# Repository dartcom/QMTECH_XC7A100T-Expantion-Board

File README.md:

# QMTECH_XC7A100T-Expantion-Board

Expantion board for the QMTECH_XC7A***T series for video processing learning.

This board contains 4 separate designs to save on cost. The boards can be ordered as a single board and then be scored with a fresh exacto knife along the dotted lines ( ! BEWARE to not breathe the FR4 dust as it is VERY harmful ! ).

The main board contains:
- 2 PMOD connectors.
- 2 24bit parallel video connectors. The left is meant to be an input and the right one an output.
- 1 micro sd card slot.
- 1 uart to usb converter.
- 1 usb PD 5v-2A input with overvoltage & overcurrent protection.
- 8 leds.

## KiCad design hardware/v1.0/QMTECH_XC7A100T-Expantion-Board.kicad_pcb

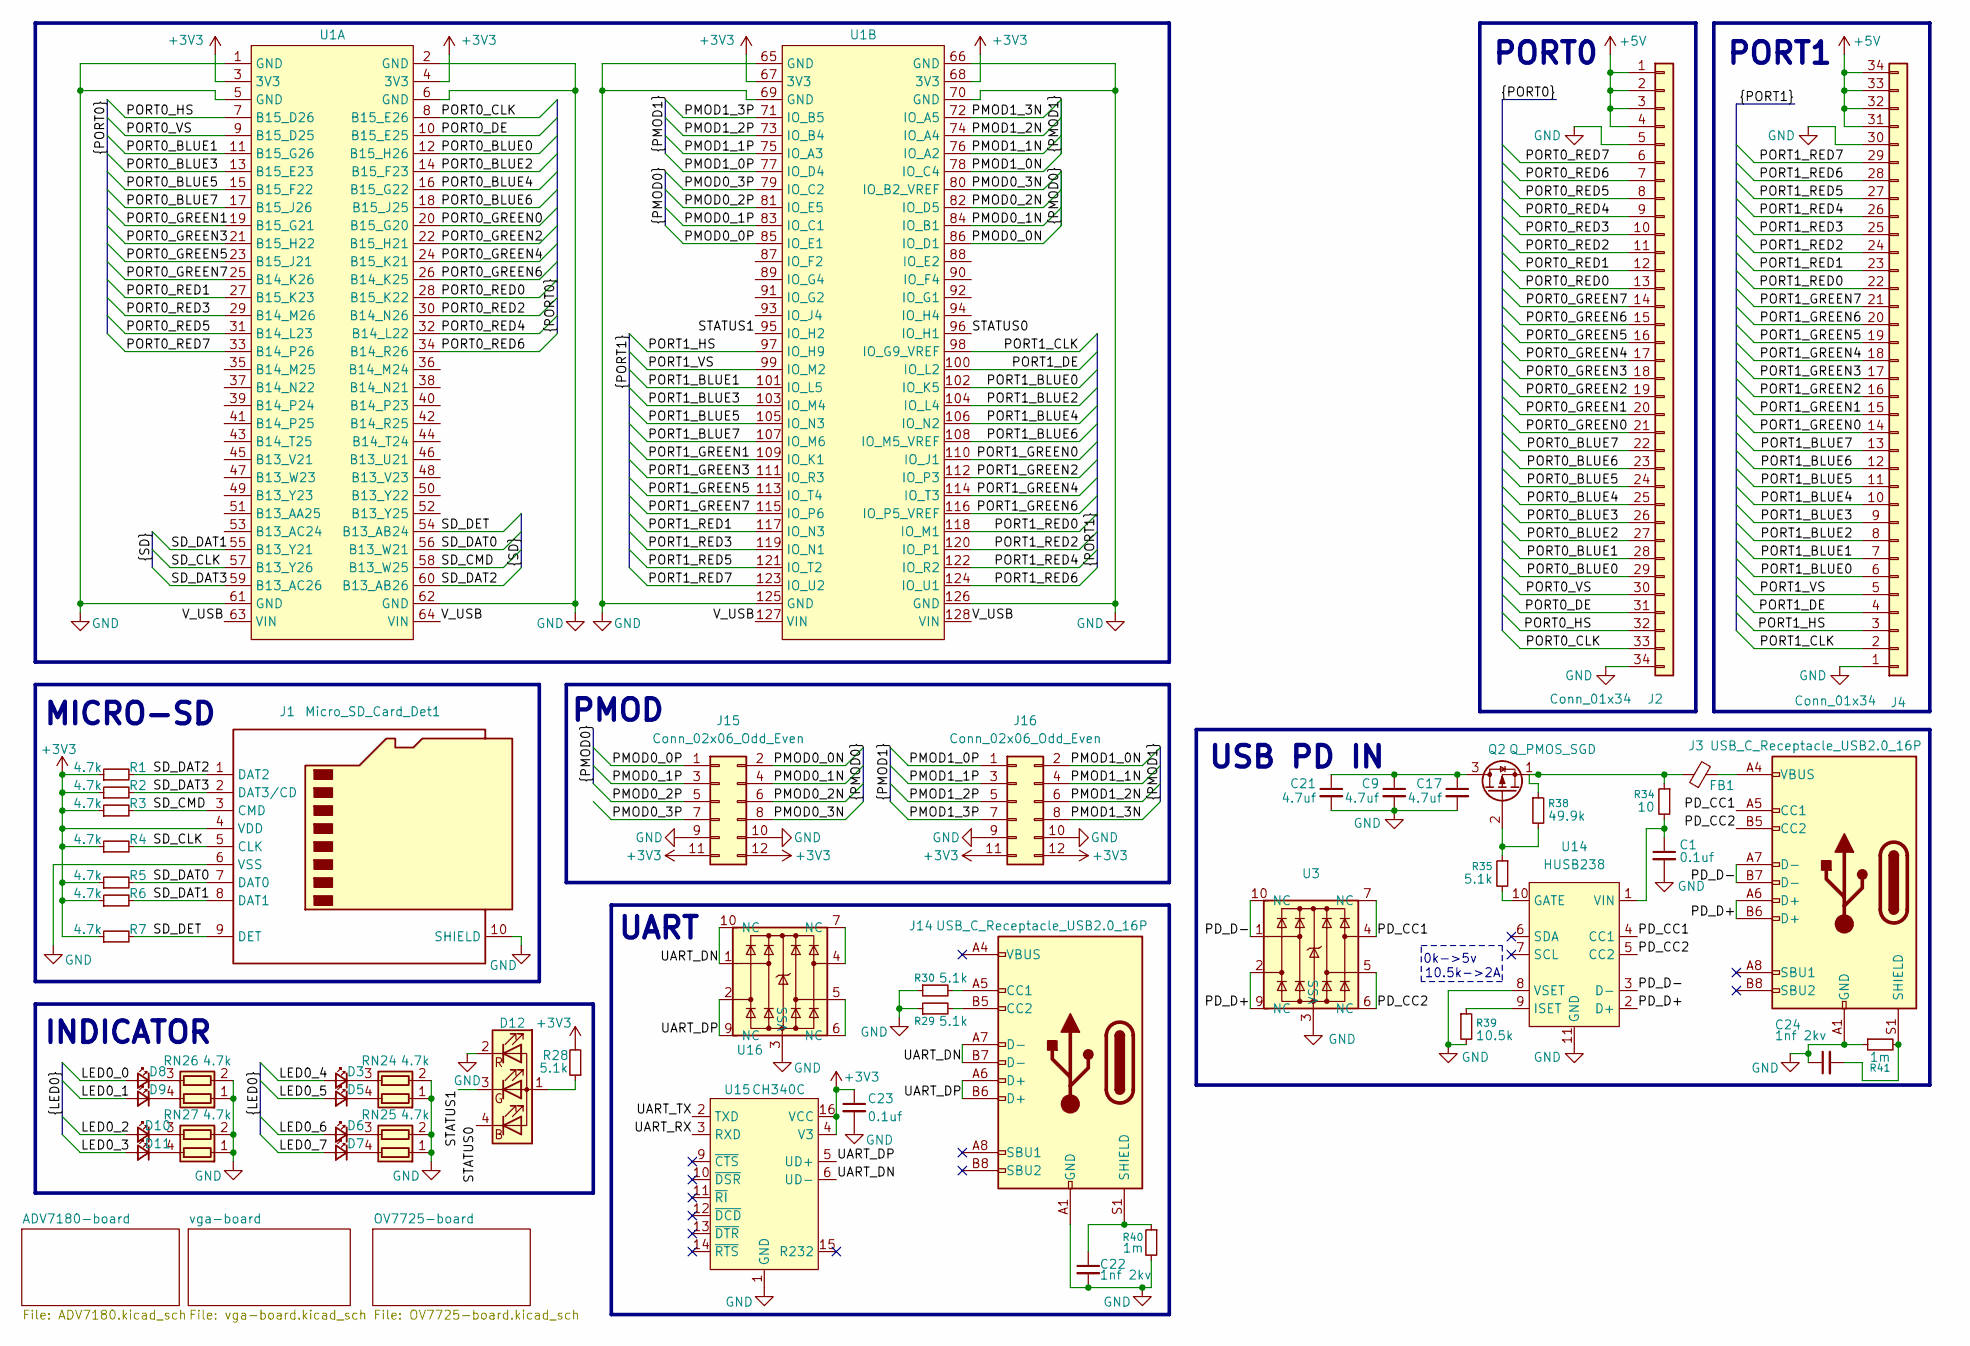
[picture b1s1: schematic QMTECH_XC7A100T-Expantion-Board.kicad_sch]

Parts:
C1, C23: 0.1uf
C9, C17, C21: 4.7uf
C22, C24: 1nf 2kv
D3, D5, D6, D7, D8, D9, D10, D11: LED_0805_2012Metric
D12: LED-SMD_4P-L1.6-W1.5-BR_TZ-P4-1615
FB1: (no value)
J1: Micro_SD_Card_Det1; TF-SMD_TF-PUSH
J2, J4: Conn_01x34; FPC-SMD_KH-FG0.5-H2.0-34PIN
J3, J14: USB_C_Receptacle_USB2.0_16P; USB_C_Receptacle_Palconn_UTC16-G
J15, J16: Conn_02x06_Odd_Even; PinSocket_2x06_P2.54mm_Horizontal
Q2: Q_PMOS_SGD; DFN-8-1EP_3x3mm_P0.5mm_EP1.7x2.4mm
R1, R2, R3, R4, R5, R6, R7: 4.7k; R_0603_1608Metric_Pad0.98x0.95mm_HandSolder
R28: 5.1k; R_0603_1608Metric_Pad0.98x0.95mm_HandSolder
R29, R30: 5.1k; R_0603_1608Metric
R34: 10
R35: 5.1k
R38: 49.9k
R39: 10.5k
R40, R41: 1m
RN24, RN25, RN26, RN27: 4.7k; R_Array_Convex_2x0603
U1: QMTECH_XC7A___T
U3, U16: Diodes_UDFN-10_1.0x2.5mm_P0.5mm
U14: HUSB238; DFN-10-1EP_3x3mm_P0.5mm_EP1.65x2.38mm_ThermalVias
U15: CH340C; SOIC-16_3.9x9.9mm_P1.27mm

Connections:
+3V3: C23.1, J1.4 (VDD), J15.11, J15.12, J16.11, J16.12, R1.1, R2.1, R3.1, R4.1, R5.1, R6.1, R7.1, R28.2, U1.3 (3V3), U1.4 (3V3), U1.67 (3V3), U1.68 (3V3), U15.4 (V3), U15.16 (VCC); also elsewhere on the board
+5V: J2.1, J2.2, J2.3, J2.4, J4.31, J4.32, J4.33, J4.34; also elsewhere on the board
/LED0_0: D8.2 (A)
/LED0_1: D9.2 (A)
/LED0_2: D10.2 (A)
/LED0_3: D11.2 (A)
/LED0_4: D3.2 (A)
/LED0_5: D5.2 (A)
/LED0_6: D6.2 (A)
/LED0_7: D7.2 (A)
/PD_CC1: J3.A5 (CC1), U3.4, U3.7 (NC), U14.4 (CC1)
/PD_CC2: J3.B5 (CC2), U3.5, U3.6 (NC), U14.5 (CC2)
/PD_D+: J3.A6 (D+), J3.B6 (D+), U3.2, U3.9 (NC), U14.2 (D+)
/PD_D-: J3.A7 (D-), J3.B7 (D-), U3.1, U3.10 (NC), U14.3 (D-)
/PMOD0_0N: J15.2, U1.86 (IO_D1)
/PMOD0_0P: J15.1, U1.85 (IO_E1)
/PMOD0_1N: J15.4, U1.84 (IO_B1)
/PMOD0_1P: J15.3, U1.83 (IO_C1)
/PMOD0_2N: J15.6, U1.82 (IO_D5)
/PMOD0_2P: J15.5, U1.81 (IO_E5)
/PMOD0_3N: J15.8, U1.80 (IO_B2_VREF)
/PMOD0_3P: J15.7, U1.79 (IO_C2)
/PMOD1_0N: J16.2, U1.78 (IO_C4)
/PMOD1_0P: J16.1, U1.77 (IO_D4)
/PMOD1_1N: J16.4, U1.76 (IO_A2)
/PMOD1_1P: J16.3, U1.75 (IO_A3)
/PMOD1_2N: J16.6, U1.74 (IO_A4)
/PMOD1_2P: J16.5, U1.73 (IO_B4)
/PMOD1_3N: J16.8, U1.72 (IO_A5)
/PMOD1_3P: J16.7, U1.71 (IO_B5)
/PORT0_BLUE0: J2.29, U1.12 (B15_H26)
/PORT0_BLUE1: J2.28, U1.11 (B15_G26)
/PORT0_BLUE2: J2.27, U1.14 (B15_F23)
/PORT0_BLUE3: J2.26, U1.13 (B15_E23)
/PORT0_BLUE4: J2.25, U1.16 (B15_G22)
/PORT0_BLUE5: J2.24, U1.15 (B15_F22)
/PORT0_BLUE6: J2.23, U1.18 (B15_J25)
/PORT0_BLUE7: J2.22, U1.17 (B15_J26)
/PORT0_CLK: J2.33, U1.8 (B15_E26)
/PORT0_DE: J2.31, U1.10 (B15_E25)
/PORT0_GREEN0: J2.21, U1.20 (B15_G20)
/PORT0_GREEN1: J2.20, U1.19 (B15_G21)
/PORT0_GREEN2: J2.19, U1.22 (B15_H21)
/PORT0_GREEN3: J2.18, U1.21 (B15_H22)
/PORT0_GREEN4: J2.17, U1.24 (B15_K21)
/PORT0_GREEN5: J2.16, U1.23 (B15_J21)
/PORT0_GREEN6: J2.15, U1.26 (B14_K25)
/PORT0_GREEN7: J2.14, U1.25 (B14_K26)
/PORT0_HS: J2.32, U1.7 (B15_D26)
/PORT0_RED0: J2.13, U1.28 (B15_K22)
/PORT0_RED1: J2.12, U1.27 (B15_K23)
/PORT0_RED2: J2.11, U1.30 (B14_N26)
/PORT0_RED3: J2.10, U1.29 (B14_M26)
/PORT0_RED4: J2.9, U1.32 (B14_L22)
/PORT0_RED5: J2.8, U1.31 (B14_L23)
/PORT0_RED6: J2.7, U1.34 (B14_R26)
/PORT0_RED7: J2.6, U1.33 (B14_P26)
/PORT0_VS: J2.30, U1.9 (B15_D25)
/PORT1_BLUE0: J4.6, U1.102 (IO_K5)
/PORT1_BLUE1: J4.7, U1.101 (IO_L5)
/PORT1_BLUE2: J4.8, U1.104 (IO_L4)
/PORT1_BLUE3: J4.9, U1.103 (IO_M4)
/PORT1_BLUE4: J4.10, U1.106 (IO_N2)
/PORT1_BLUE5: J4.11, U1.105 (IO_N3)
/PORT1_BLUE6: J4.12, U1.108 (IO_M5_VREF)
/PORT1_BLUE7: J4.13, U1.107 (IO_M6)
/PORT1_CLK: J4.2, U1.98 (IO_G9_VREF)
/PORT1_DE: J4.4, U1.100 (IO_L2)
/PORT1_GREEN0: J4.14, U1.110 (IO_J1)
/PORT1_GREEN1: J4.15, U1.109 (IO_K1)
/PORT1_GREEN2: J4.16, U1.112 (IO_P3)
/PORT1_GREEN3: J4.17, U1.111 (IO_R3)
/PORT1_GREEN4: J4.18, U1.114 (IO_T3)
/PORT1_GREEN5: J4.19, U1.113 (IO_T4)
/PORT1_GREEN6: J4.20, U1.116 (IO_P5_VREF)
/PORT1_GREEN7: J4.21, U1.115 (IO_P6)
/PORT1_HS: J4.3, U1.97 (IO_H9)
/PORT1_RED0: J4.22, U1.118 (IO_M1)
/PORT1_RED1: J4.23, U1.117 (IO_N3)
/PORT1_RED2: J4.24, U1.120 (IO_P1)
/PORT1_RED3: J4.25, U1.119 (IO_N1)
/PORT1_RED4: J4.26, U1.122 (IO_R2)
/PORT1_RED5: J4.27, U1.121 (IO_T2)
/PORT1_RED6: J4.28, U1.124 (IO_U1)
/PORT1_RED7: J4.29, U1.123 (IO_U2)
/PORT1_VS: J4.5, U1.99 (IO_M2)
/SD_CLK: J1.5 (CLK), R4.2, U1.57 (B13_Y26)
/SD_CMD: J1.3 (CMD), R3.2, U1.58 (B13_W25)
/SD_DAT0: J1.7 (DAT0), R5.2, U1.56 (B13_W21)
/SD_DAT1: J1.8 (DAT1), R6.2, U1.55 (B13_Y21)
/SD_DAT2: J1.1 (DAT2), R1.2, U1.60 (B13_AB26)
/SD_DAT3: J1.2 (DAT3/CD), R2.2, U1.59 (B13_AC26)
/SD_DET: J1.9 (DET), R7.2, U1.54 (B13_AB24)
/STATUS0: D12.4 (BK), U1.96 (IO_H1)
/STATUS1: D12.3 (GK), U1.95 (IO_H2)
/UART_DN: J14.A7 (D-), J14.B7 (D-), U15.6 (UD-), U16.1, U16.10 (NC)
/UART_DP: J14.A6 (D+), J14.B6 (D+), U15.5 (UD+), U16.2, U16.9 (NC)
/UART_RX: U15.3 (RXD)
/UART_TX: U15.2 (TXD)
/V_USB: U1.63 (VIN), U1.64 (VIN), U1.127 (VIN), U1.128 (VIN)
GND: C1.2, C9.2, C17.2, C21.2, C22.2, C23.2, C24.1, D12.2 (RK), J1.6 (VSS), J1.10 (SHIELD), J2.5, J2.34, J3.A1 (GND), J3.A12 (GND), J3.B1 (GND), J3.B12 (GND), J4.1, J4.30, J14.A1 (GND), J14.A12 (GND), J14.B1 (GND), J14.B12 (GND), J15.9, J15.10, J16.9, J16.10, R29.1, R30.1, R39.2, R40.2, R41.1, RN24.1 (R1.1), RN24.2 (R2.1), RN25.1 (R1.1), RN25.2 (R2.1), RN26.1 (R1.1), RN26.2 (R2.1), RN27.1 (R1.1), RN27.2 (R2.1), U1.1 (GND), U1.2 (GND), U1.5 (GND), U1.6 (GND), U1.61 (GND), U1.62 (GND), U1.65 (GND), U1.66 (GND), U1.69 (GND), U1.70 (GND), U1.125 (GND), U1.126 (GND), U3.3 (VSS), U3.8 (VSS), U14.8 (VSET), U14.11 (GND), U15.1 (GND), U16.3 (VSS), U16.8 (VSS); also elsewhere on the board
unnamed: D3.1 (K), RN24.3 (R2.2)
unnamed: D5.1 (K), RN24.4 (R1.2)
unnamed: D6.1 (K), RN25.3 (R2.2)
unnamed: D7.1 (K), RN25.4 (R1.2)
unnamed: D8.1 (K), RN26.3 (R2.2)
unnamed: D9.1 (K), RN26.4 (R1.2)
unnamed: D10.1 (K), RN27.3 (R2.2)
unnamed: D11.1 (K), RN27.4 (R1.2)
unnamed: D12.1 (A), R28.1
unnamed: FB1.2, J3.A4 (VBUS), J3.A9 (VBUS), J3.B4 (VBUS), J3.B9 (VBUS)
unnamed: C24.2, J3.S1 (SHIELD), R41.2
unnamed: J14.A5 (CC1), R30.2
unnamed: J14.B5 (CC2), R29.2
unnamed: C22.1, J14.S1 (SHIELD), R40.1
unnamed: C9.1, C17.1, C21.1, Q2.3 (D)
unnamed: Q2.2 (G), R35.1, R38.2
unnamed: FB1.1, Q2.1 (S), R34.1, R38.1
unnamed: R35.2, U14.10 (GATE)
unnamed: R39.1, U14.9 (ISET)
unnamed: C1.1, R34.2, U14.1 (VIN)
unnamed: U16.5, U16.6 (NC)
unnamed: U16.4, U16.7 (NC)

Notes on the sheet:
PORT0
PORT1
PMOD
MICRO-SD
10.5k->2A
UART
USB PD IN
0k->5v
INDICATOR

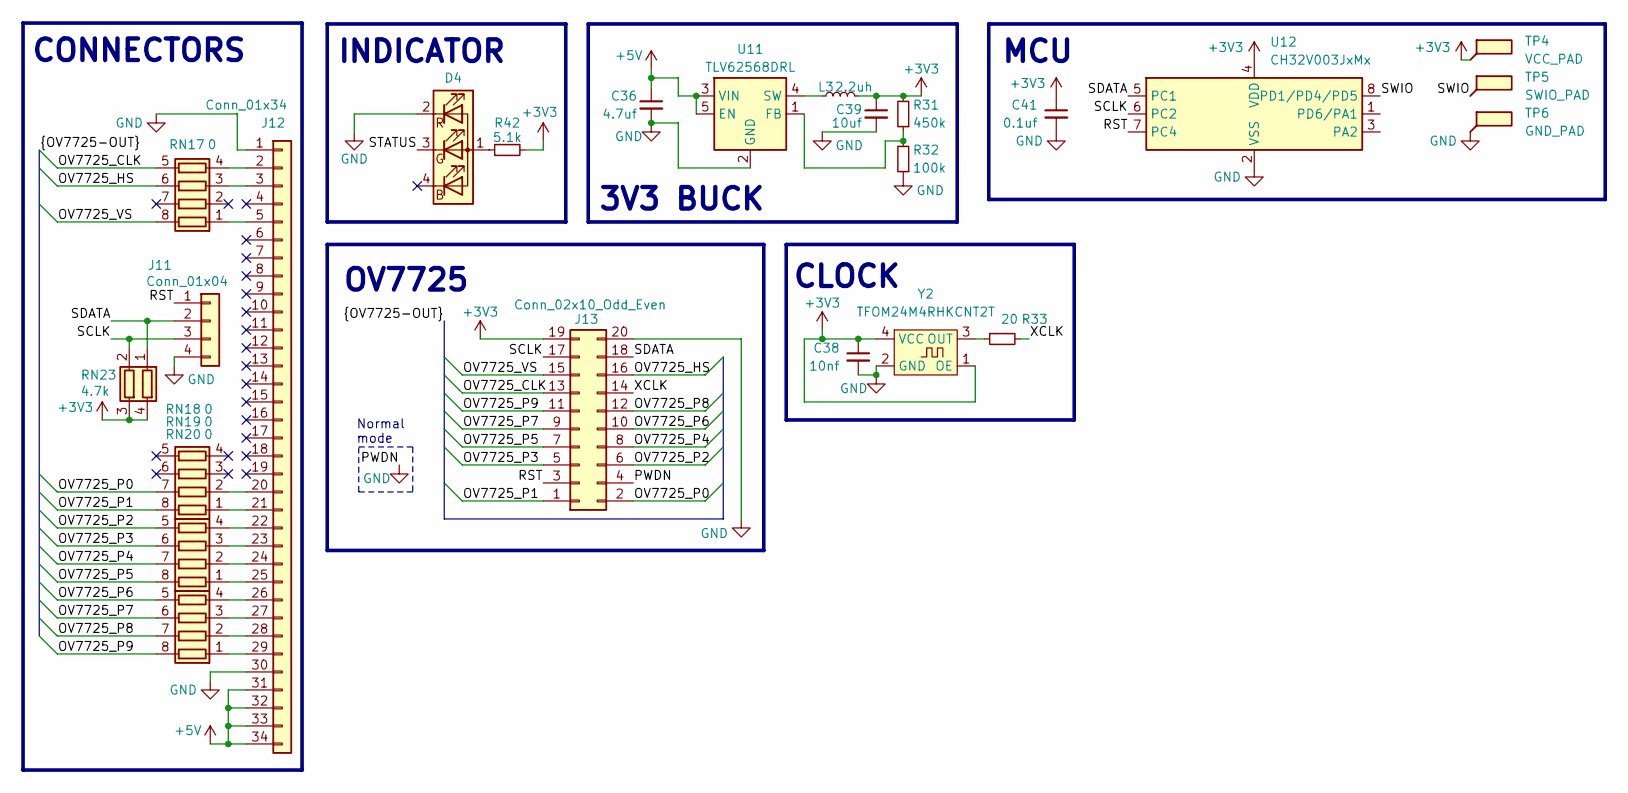
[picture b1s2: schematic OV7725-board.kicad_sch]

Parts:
C36: 4.7uf; C_0603_1608Metric
C38: 10nf; C_0603_1608Metric
C39: 10uf; C_0603_1608Metric
C41: 0.1uf; C_0603_1608Metric
D4: LED-SMD_4P-L1.6-W1.5-BR_TZ-P4-1615
J11: Conn_01x04; PinHeader_1x04_P2.54mm_Vertical
J12: Conn_01x34; FPC-SMD_KH-FG0.5-H2.0-34PIN
J13: Conn_02x10_Odd_Even; PinSocket_2x10_P2.54mm_Vertical
L3: 2.2uh; L_0603_1608Metric
R31: 450k; R_0603_1608Metric
R32: 100k; R_0603_1608Metric
R33: 20; R_0603_1608Metric
R42: 5.1k; R_0603_1608Metric
RN17, RN18, RN19, RN20: 0; R_Array_Convex_4x0603
RN23: 4.7k; R_Array_Convex_2x0603
TP4: VCC_PAD; TestPoint_Pad_D1.5mm
TP5: SWIO_PAD; TestPoint_Pad_D1.5mm
TP6: GND_PAD; TestPoint_Pad_D1.5mm
U11: TLV62568DRL; SOT-563
U12: CH32V003JxMx; SOP-8_3.9x4.9mm_P1.27mm
Y2: TFOM24M4RHKCNT2T

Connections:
+3V3: C38.1, C39.1, C41.1, J13.19, L3.2, R31.2, R42.2, RN23.3 (R2.2), RN23.4 (R1.2), TP4.1, U12.4 (VDD), Y2.1 (OE), Y2.4 (VCC); also elsewhere on the board
+5V: C36.1, J12.31, J12.32, J12.33, J12.34, U11.3 (VIN), U11.5 (EN); also elsewhere on the board
/OV7725-board/OV7725_CLK: J13.13, RN17.5 (R4.2)
/OV7725-board/OV7725_HS: J13.16, RN17.6 (R3.2)
/OV7725-board/OV7725_P0: J13.2, RN18.7 (R2.2)
/OV7725-board/OV7725_P1: J13.1, RN18.8 (R1.2)
/OV7725-board/OV7725_P2: J13.6, RN19.5 (R4.2)
/OV7725-board/OV7725_P3: J13.5, RN19.6 (R3.2)
/OV7725-board/OV7725_P4: J13.8, RN19.7 (R2.2)
/OV7725-board/OV7725_P5: J13.7, RN19.8 (R1.2)
/OV7725-board/OV7725_P6: J13.10, RN20.5 (R4.2)
/OV7725-board/OV7725_P7: J13.9, RN20.6 (R3.2)
/OV7725-board/OV7725_P8: J13.12, RN20.7 (R2.2)
/OV7725-board/OV7725_P9: J13.11, RN20.8 (R1.2)
/OV7725-board/OV7725_VS: J13.15, RN17.8 (R1.2)
/OV7725-board/RST: J11.1, J13.3, U12.7 (PC4)
/OV7725-board/SCLK: J11.3, J13.17, RN23.2 (R2.1), U12.6 (PC2)
/OV7725-board/SDATA: J11.2, J13.18, RN23.1 (R1.1), U12.5 (PC1)
/OV7725-board/STATUS: D4.3 (GK)
/OV7725-board/SWIO: TP5.1, U12.8 (PD1/PD4/PD5)
/OV7725-board/XCLK: J13.14, R33.2
GND: C36.2, C38.2, C39.2, C41.2, D4.2 (RK), J11.4, J12.1, J12.30, J13.4, J13.20, R32.1, TP6.1, U11.2 (GND), U12.2 (VSS), Y2.2 (GND); also elsewhere on the board
unnamed: D4.1 (A), R42.1
unnamed: J12.2, RN17.4 (R4.1)
unnamed: J12.3, RN17.3 (R3.1)
unnamed: J12.5, RN17.1 (R1.1)
unnamed: J12.20, RN18.2 (R2.1)
unnamed: J12.21, RN18.1 (R1.1)
unnamed: J12.22, RN19.4 (R4.1)
unnamed: J12.23, RN19.3 (R3.1)
unnamed: J12.24, RN19.2 (R2.1)
unnamed: J12.25, RN19.1 (R1.1)
unnamed: J12.26, RN20.4 (R4.1)
unnamed: J12.27, RN20.3 (R3.1)
unnamed: J12.28, RN20.2 (R2.1)
unnamed: J12.29, RN20.1 (R1.1)
unnamed: R31.1, R32.2, U11.1 (FB)
unnamed: L3.1, U11.4 (SW)
unnamed: R33.1, Y2.3 (OUT)

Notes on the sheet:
CLOCK
MCU
OV7725
INDICATOR
Normal mode
CONNECTORS
3V3 BUCK

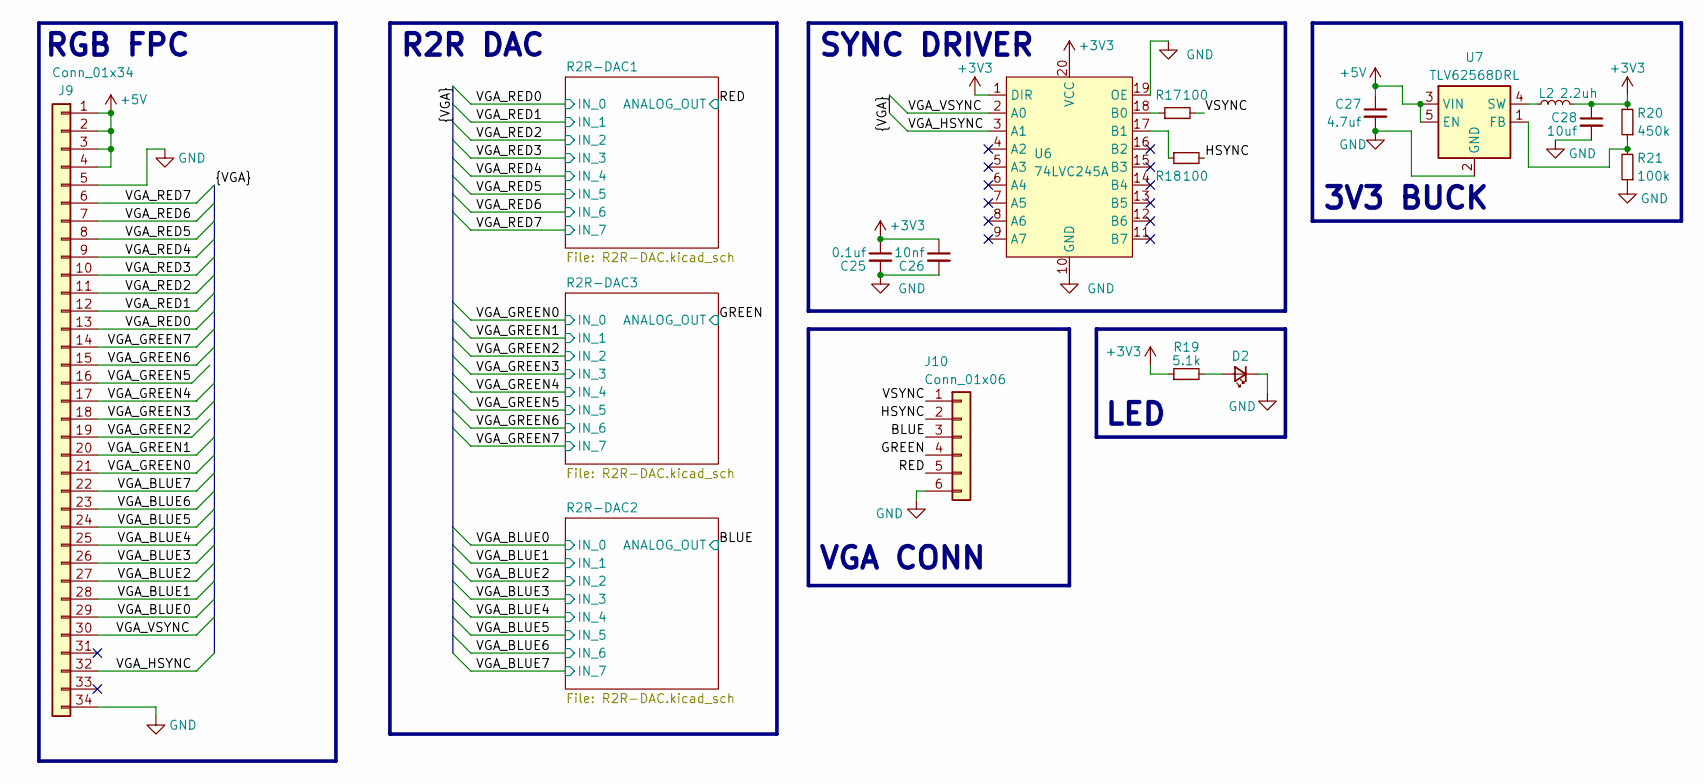
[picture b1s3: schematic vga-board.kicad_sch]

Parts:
C25: 0.1uf; C_0603_1608Metric
C26: 10nf; C_0603_1608Metric
C27: 4.7uf; C_0603_1608Metric
C28: 10uf; C_0603_1608Metric
D2: LED_0402_1005Metric_Pad0.77x0.64mm_HandSolder
J9: Conn_01x34; FPC-SMD_KH-FG0.5-H2.0-34PIN
J10: Conn_01x06; PinHeader_1x06_P2.54mm_Vertical
L2: 2.2uh; L_0603_1608Metric
R17, R18: 100; R_0603_1608Metric
R19: 5.1k; R_0603_1608Metric
R20: 450k; R_0603_1608Metric
R21: 100k; R_0603_1608Metric
U6: 74LVC245A; TSSOP-20_4.4x6.5mm_P0.65mm
U7: TLV62568DRL; SOT-563

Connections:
+3V3: C25.1, C26.1, C28.1, L2.2, R19.1, R20.2, U6.1 (DIR), U6.20 (VCC); also elsewhere on the board
+5V: C27.1, J9.1, J9.2, J9.3, J9.4, U7.3 (VIN), U7.5 (EN); also elsewhere on the board
/vga-board/BLUE: J10.3; also elsewhere on the board
/vga-board/GREEN: J10.4; also elsewhere on the board
/vga-board/HSYNC: J10.2, R18.2
/vga-board/RED: J10.5; also elsewhere on the board
/vga-board/VGA_BLUE0: J9.29; also elsewhere on the board
/vga-board/VGA_BLUE1: J9.28; also elsewhere on the board
/vga-board/VGA_BLUE2: J9.27; also elsewhere on the board
/vga-board/VGA_BLUE3: J9.26; also elsewhere on the board
/vga-board/VGA_BLUE4: J9.25; also elsewhere on the board
/vga-board/VGA_BLUE5: J9.24; also elsewhere on the board
/vga-board/VGA_BLUE6: J9.23; also elsewhere on the board
/vga-board/VGA_BLUE7: J9.22; also elsewhere on the board
/vga-board/VGA_GREEN0: J9.21; also elsewhere on the board
/vga-board/VGA_GREEN1: J9.20; also elsewhere on the board
/vga-board/VGA_GREEN2: J9.19; also elsewhere on the board
/vga-board/VGA_GREEN3: J9.18; also elsewhere on the board
/vga-board/VGA_GREEN4: J9.17; also elsewhere on the board
/vga-board/VGA_GREEN5: J9.16; also elsewhere on the board
/vga-board/VGA_GREEN6: J9.15; also elsewhere on the board
/vga-board/VGA_GREEN7: J9.14; also elsewhere on the board
/vga-board/VGA_HSYNC: J9.32, U6.3 (A1)
/vga-board/VGA_RED0: J9.13; also elsewhere on the board
/vga-board/VGA_RED1: J9.12; also elsewhere on the board
/vga-board/VGA_RED2: J9.11; also elsewhere on the board
/vga-board/VGA_RED3: J9.10; also elsewhere on the board
/vga-board/VGA_RED4: J9.9; also elsewhere on the board
/vga-board/VGA_RED5: J9.8; also elsewhere on the board
/vga-board/VGA_RED6: J9.7; also elsewhere on the board
/vga-board/VGA_RED7: J9.6; also elsewhere on the board
/vga-board/VGA_VSYNC: J9.30, U6.2 (A0)
/vga-board/VSYNC: J10.1, R17.2
GND: C25.2, C26.2, C27.2, C28.2, D2.1 (K), J9.5, J9.34, J10.6, R21.1, U6.10 (GND), U6.19 (OE), U7.2 (GND); also elsewhere on the board
unnamed: D2.2 (A), R19.2
unnamed: R17.1, U6.18 (B0)
unnamed: R18.1, U6.17 (B1)
unnamed: R20.1, R21.2, U7.1 (FB)
unnamed: L2.1, U7.4 (SW)

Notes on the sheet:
R2R DAC
LED
3V3 BUCK
RGB FPC
SYNC DRIVER
VGA CONN

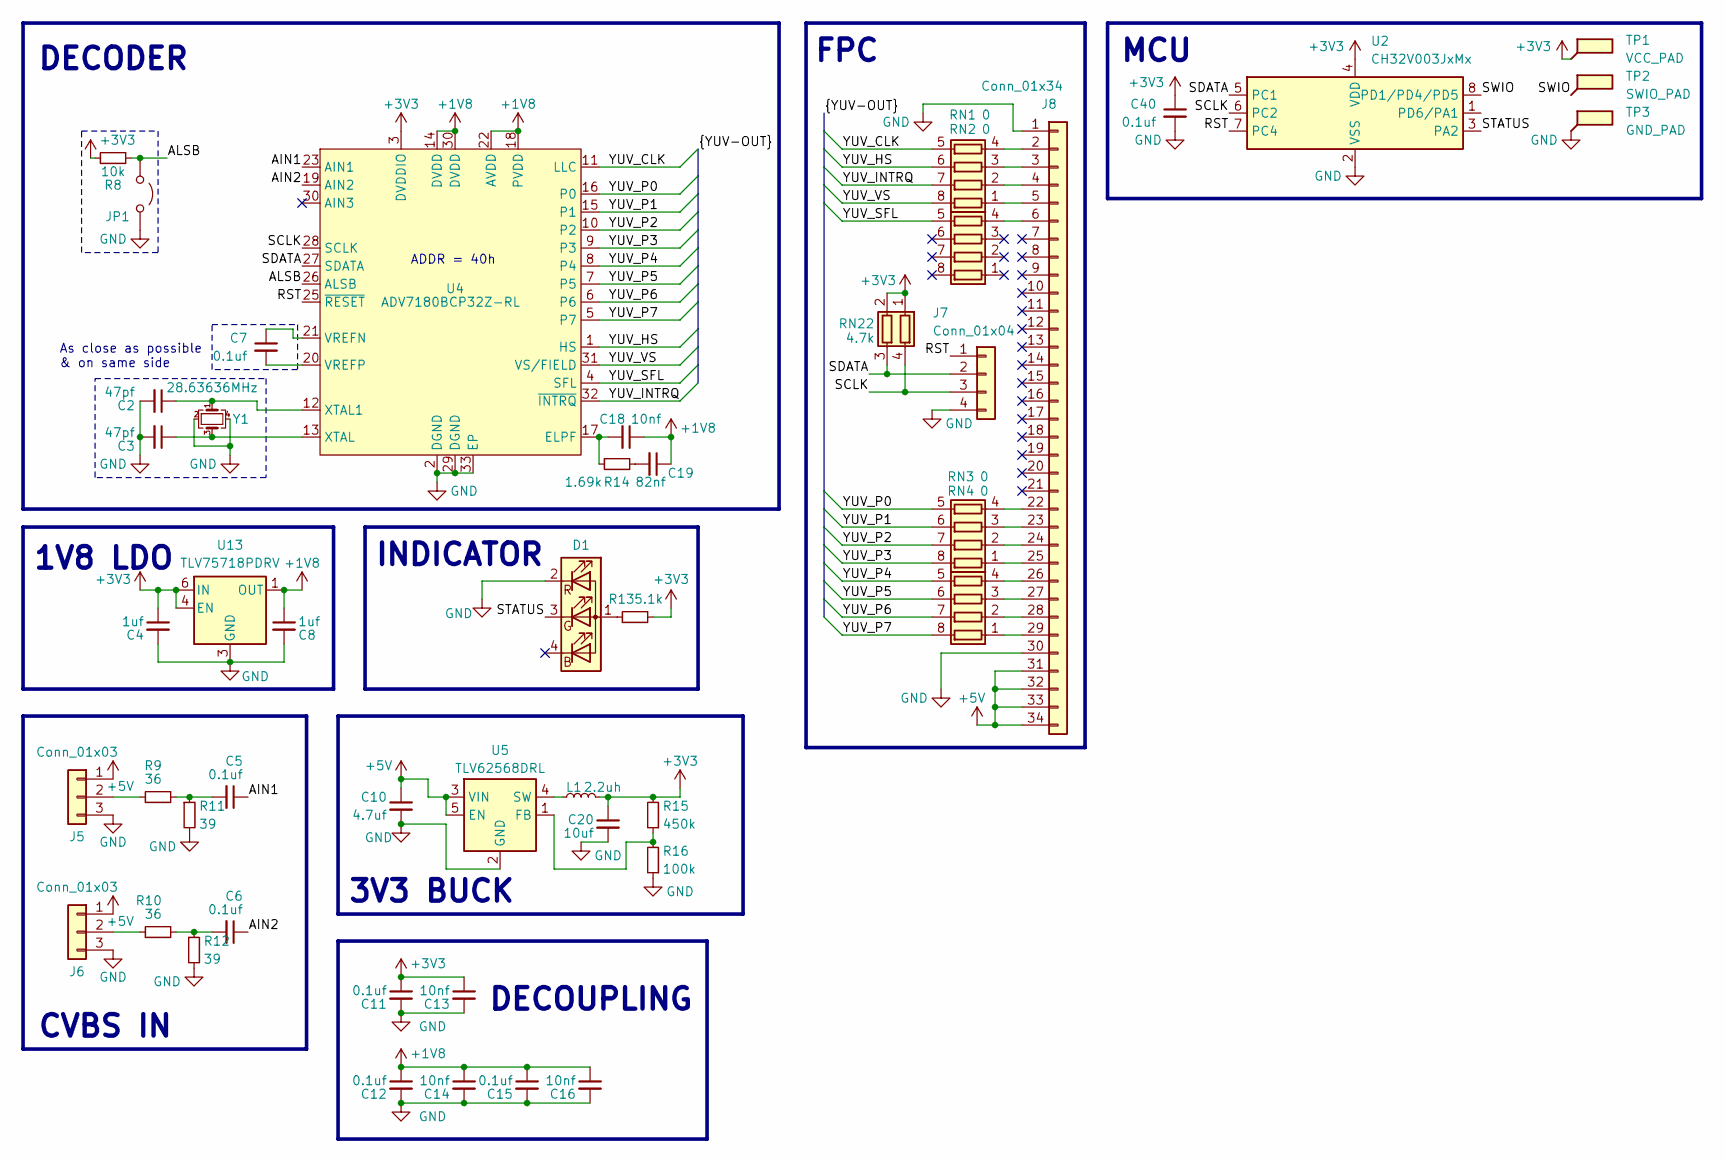
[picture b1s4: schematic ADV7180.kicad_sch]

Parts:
C2, C3: 47pf; C_0603_1608Metric
C4, C8: 1uf; C_0603_1608Metric
C5, C6, C7, C11, C12, C15, C40: 0.1uf; C_0603_1608Metric
C10: 4.7uf; C_0603_1608Metric
C13, C14, C16, C18: 10nf; C_0603_1608Metric
C19: 82nf; C_0603_1608Metric
C20: 10uf; C_0603_1608Metric
D1: LED-SMD_4P-L1.6-W1.5-BR_TZ-P4-1615
J5, J6: Conn_01x03; PinHeader_1x03_P2.54mm_Vertical
J7: Conn_01x04; PinHeader_1x04_P2.54mm_Vertical
J8: Conn_01x34; FPC-SMD_KH-FG0.5-H2.0-34PIN
JP1: SolderJumper-2_P1.3mm_Open_RoundedPad1.0x1.5mm
L1: 2.2uh; L_0603_1608Metric
R8: 10k; R_0603_1608Metric
R9, R10: 36; R_0603_1608Metric
R11, R12: 39; R_0603_1608Metric
R13: 5.1k; R_0603_1608Metric
R14: 1.69k; R_0603_1608Metric
R15: 450k; R_0603_1608Metric
R16: 100k; R_0603_1608Metric
RN1, RN2, RN3, RN4: 0; R_Array_Convex_4x0603
RN22: 4.7k; R_Array_Convex_2x0603
TP1: VCC_PAD; TestPoint_Pad_D1.5mm
TP2: SWIO_PAD; TestPoint_Pad_D1.5mm
TP3: GND_PAD; TestPoint_Pad_D1.5mm
U2: CH32V003JxMx; SOP-8_3.9x4.9mm_P1.27mm
U4: ADV7180BCP32Z-RL; LFCSP-32-1EP_5x5mm_P0.5mm_EP3.6x3.6mm; LCSC Part C459884
U5: TLV62568DRL; SOT-563
U13: TLV75718PDRV; WSON-6-1EP_2x2mm_P0.65mm_EP1x1.6mm
Y1: 28.63636MHz; Crystal_SMD_Abracon_ABM8AIG-4Pin_3.2x2.5mm

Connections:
+1V8: C8.1, C12.1, C14.1, C15.1, C16.1, C18.1, C19.1, U4.14 (DVDD), U4.18 (PVDD), U4.22 (AVDD), U4.30 (DVDD), U13.1 (OUT)
+3V3: C4.1, C11.1, C13.1, C20.1, C40.1, L1.2, R8.2, R13.2, R15.2, RN22.1 (R1.1), RN22.2 (R2.1), TP1.1, U2.4 (VDD), U4.3 (DVDDIO), U13.4 (EN), U13.6 (IN); also elsewhere on the board
+5V: C10.1, J5.1, J6.1, J8.31, J8.32, J8.33, J8.34, U5.3 (VIN), U5.5 (EN); also elsewhere on the board
/ADV7180-board/AIN1: C5.1, U4.23 (AIN1)
/ADV7180-board/AIN2: C6.1, U4.19 (AIN2)
/ADV7180-board/ALSB: JP1.2 (B), R8.1, U4.26 (ALSB)
/ADV7180-board/RST: J7.1, U2.7 (PC4), U4.25 (~RESET)
/ADV7180-board/SCLK: J7.3, RN22.4 (R1.2), U2.6 (PC2), U4.28 (SCLK)
/ADV7180-board/SDATA: J7.2, RN22.3 (R2.2), U2.5 (PC1), U4.27 (SDATA)
/ADV7180-board/STATUS: D1.3 (GK), U2.3 (PA2)
/ADV7180-board/SWIO: TP2.1, U2.8 (PD1/PD4/PD5)
/ADV7180-board/YUV_CLK: RN1.5 (R4.2), U4.11 (LLC)
/ADV7180-board/YUV_HS: RN1.6 (R3.2), U4.1 (HS)
/ADV7180-board/YUV_INTRQ: RN1.7 (R2.2), U4.32 (~INTRQ)
/ADV7180-board/YUV_P0: RN3.5 (R4.2), U4.16 (P0)
/ADV7180-board/YUV_P1: RN3.6 (R3.2), U4.15 (P1)
/ADV7180-board/YUV_P2: RN3.7 (R2.2), U4.10 (P2)
/ADV7180-board/YUV_P3: RN3.8 (R1.2), U4.9 (P3)
/ADV7180-board/YUV_P4: RN4.5 (R4.2), U4.8 (P4)
/ADV7180-board/YUV_P5: RN4.6 (R3.2), U4.7 (P5)
/ADV7180-board/YUV_P6: RN4.7 (R2.2), U4.6
/ADV7180-board/YUV_P7: RN4.8 (R1.2), U4.5 (P7)
/ADV7180-board/YUV_SFL: RN2.5 (R4.2), U4.4 (SFL)
/ADV7180-board/YUV_VS: RN1.8 (R1.2), U4.31 (VS/FIELD)
GND: C2.2, C3.2, C4.2, C8.2, C10.2, C11.2, C12.2, C13.2, C14.2, C15.2, C16.2, C20.2, C40.2, D1.2 (RK), J5.3, J6.3, J7.4, J8.1, J8.30, JP1.1 (A), R11.2, R12.2, R16.1, TP3.1, U2.2 (VSS), U4.2 (DGND), U4.29 (DGND), U4.33 (EP), U5.2 (GND), U13.3 (GND), U13.7 (GND), Y1.2, Y1.4; also elsewhere on the board
unnamed: C5.2, R9.2, R11.1
unnamed: C6.2, R10.2, R12.1
unnamed: C19.2, R14.2
unnamed: D1.1 (A), R13.1
unnamed: J5.2, R9.1
unnamed: J6.2, R10.1
unnamed: J8.2, RN1.4 (R4.1)
unnamed: J8.3, RN1.3 (R3.1)
unnamed: J8.4, RN1.2 (R2.1)
unnamed: J8.5, RN1.1 (R1.1)
unnamed: J8.6, RN2.4 (R4.1)
unnamed: J8.22, RN3.4 (R4.1)
unnamed: J8.23, RN3.3 (R3.1)
unnamed: J8.24, RN3.2 (R2.1)
unnamed: J8.25, RN3.1 (R1.1)
unnamed: J8.26, RN4.4 (R4.1)
unnamed: J8.27, RN4.3 (R3.1)
unnamed: J8.28, RN4.2 (R2.1)
unnamed: J8.29, RN4.1 (R1.1)
unnamed: C18.2, R14.1, U4.17 (ELPF)
unnamed: C7.1, U4.21 (VREFN)
unnamed: C7.2, U4.20 (VREFP)
unnamed: C2.1, U4.12 (XTAL1), Y1.1
unnamed: C3.1, U4.13 (XTAL), Y1.3
unnamed: R15.1, R16.2, U5.1 (FB)
unnamed: L1.1, U5.4 (SW)

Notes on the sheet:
3V3 BUCK
As close as possible & on same side
1V8 LDO
FPC
MCU
ADDR = 40h
DECOUPLING
INDICATOR
DECODER
CVBS IN

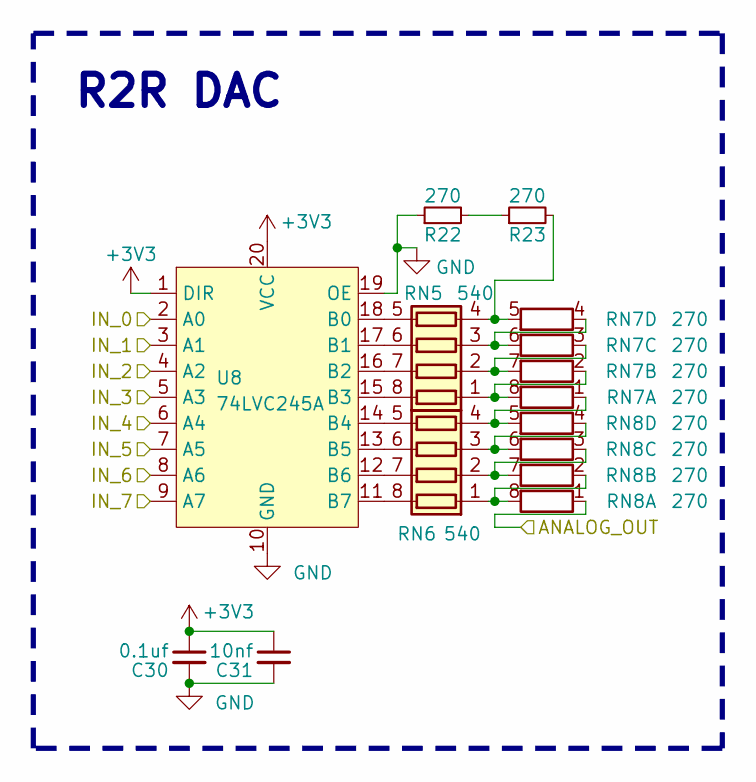
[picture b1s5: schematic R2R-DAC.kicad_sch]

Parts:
C30: 0.1uf; C_0603_1608Metric
C31: 10nf; C_0603_1608Metric
R22, R23: 270; R_0603_1608Metric
RN5, RN6: 540; R_Array_Convex_4x0603
RN7, RN8: 270; R_Array_Convex_4x0603
U8: 74LVC245A; TSSOP-20_4.4x6.5mm_P0.65mm

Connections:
+3V3: C30.1, C31.1, U8.1 (DIR), U8.20 (VCC); also elsewhere on the board
/vga-board/RED: RN8.1 (R1.1); also elsewhere on the board
/vga-board/VGA_RED0: U8.2 (A0); also elsewhere on the board
/vga-board/VGA_RED1: U8.3 (A1); also elsewhere on the board
/vga-board/VGA_RED2: U8.4 (A2); also elsewhere on the board
/vga-board/VGA_RED3: U8.5 (A3); also elsewhere on the board
/vga-board/VGA_RED4: U8.6 (A4); also elsewhere on the board
/vga-board/VGA_RED5: U8.7 (A5); also elsewhere on the board
/vga-board/VGA_RED6: U8.8 (A6); also elsewhere on the board
/vga-board/VGA_RED7: U8.9 (A7); also elsewhere on the board
GND: C30.2, C31.2, R22.1, U8.10 (GND), U8.19 (OE); also elsewhere on the board
unnamed: R22.2, R23.1
unnamed: RN5.1 (R1.1), RN7.2 (R2.1), RN7.8 (R1.2)
unnamed: RN5.8 (R1.2), U8.15 (B3)
unnamed: RN5.2 (R2.1), RN7.3 (R3.1), RN7.7 (R2.2)
unnamed: RN5.7 (R2.2), U8.16 (B2)
unnamed: RN5.3 (R3.1), RN7.4 (R4.1), RN7.6 (R3.2)
unnamed: RN5.6 (R3.2), U8.17 (B1)
unnamed: R23.2, RN5.4 (R4.1), RN7.5 (R4.2)
unnamed: RN5.5 (R4.2), U8.18 (B0)
unnamed: RN6.1 (R1.1), RN8.2 (R2.1), RN8.8 (R1.2)
unnamed: RN6.8 (R1.2), U8.11 (B7)
unnamed: RN6.2 (R2.1), RN8.3 (R3.1), RN8.7 (R2.2)
unnamed: RN6.7 (R2.2), U8.12 (B6)
unnamed: RN6.3 (R3.1), RN8.4 (R4.1), RN8.6 (R3.2)
unnamed: RN6.6 (R3.2), U8.13 (B5)
unnamed: RN6.4 (R4.1), RN7.1 (R1.1), RN8.5 (R4.2)
unnamed: RN6.5 (R4.2), U8.14 (B4)

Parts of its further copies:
C32, C34: 0.1uf; C_0603_1608Metric
C33, C35: 10nf; C_0603_1608Metric
R24, R25, R26, R27: 270; R_0603_1608Metric
RN9, RN10, RN13, RN14: 540; R_Array_Convex_4x0603
RN11, RN12, RN15, RN16: 270; R_Array_Convex_4x0603
U9, U10: 74LVC245A; TSSOP-20_4.4x6.5mm_P0.65mm

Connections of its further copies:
+3V3: C32.1, C33.1, C34.1, C35.1, U9.1 (DIR), U9.20 (VCC), U10.1 (DIR), U10.20 (VCC); also elsewhere on the board
/vga-board/BLUE: RN12.1 (R1.1); also elsewhere on the board
/vga-board/GREEN: RN16.1 (R1.1); also elsewhere on the board
/vga-board/VGA_BLUE0: U9.2 (A0); also elsewhere on the board
/vga-board/VGA_BLUE1: U9.3 (A1); also elsewhere on the board
/vga-board/VGA_BLUE2: U9.4 (A2); also elsewhere on the board
/vga-board/VGA_BLUE3: U9.5 (A3); also elsewhere on the board
/vga-board/VGA_BLUE4: U9.6 (A4); also elsewhere on the board
/vga-board/VGA_BLUE5: U9.7 (A5); also elsewhere on the board
/vga-board/VGA_BLUE6: U9.8 (A6); also elsewhere on the board
/vga-board/VGA_BLUE7: U9.9 (A7); also elsewhere on the board
/vga-board/VGA_GREEN0: U10.2 (A0); also elsewhere on the board
/vga-board/VGA_GREEN1: U10.3 (A1); also elsewhere on the board
/vga-board/VGA_GREEN2: U10.4 (A2); also elsewhere on the board
/vga-board/VGA_GREEN3: U10.5 (A3); also elsewhere on the board
/vga-board/VGA_GREEN4: U10.6 (A4); also elsewhere on the board
/vga-board/VGA_GREEN5: U10.7 (A5); also elsewhere on the board
/vga-board/VGA_GREEN6: U10.8 (A6); also elsewhere on the board
/vga-board/VGA_GREEN7: U10.9 (A7); also elsewhere on the board
GND: C32.2, C33.2, C34.2, C35.2, R24.1, R26.1, U9.10 (GND), U9.19 (OE), U10.10 (GND), U10.19 (OE); also elsewhere on the board
unnamed: R24.2, R25.1
unnamed: R26.2, R27.1
unnamed: RN9.8 (R1.2), U9.15 (B3)
unnamed: RN9.7 (R2.2), U9.16 (B2)
unnamed: RN9.6 (R3.2), U9.17 (B1)
unnamed: RN9.5 (R4.2), U9.18 (B0)
unnamed: RN10.1 (R1.1), RN12.2 (R2.1), RN12.8 (R1.2)
unnamed: RN10.8 (R1.2), U9.11 (B7)
unnamed: RN10.2 (R2.1), RN12.3 (R3.1), RN12.7 (R2.2)
unnamed: RN10.7 (R2.2), U9.12 (B6)
unnamed: RN10.3 (R3.1), RN12.4 (R4.1), RN12.6 (R3.2)
unnamed: RN10.6 (R3.2), U9.13 (B5)
unnamed: RN10.4 (R4.1), RN11.1 (R1.1), RN12.5 (R4.2)
unnamed: RN10.5 (R4.2), U9.14 (B4)
unnamed: RN9.1 (R1.1), RN11.2 (R2.1), RN11.8 (R1.2)
unnamed: RN9.2 (R2.1), RN11.3 (R3.1), RN11.7 (R2.2)
unnamed: RN9.3 (R3.1), RN11.4 (R4.1), RN11.6 (R3.2)
unnamed: R25.2, RN9.4 (R4.1), RN11.5 (R4.2)
unnamed: RN13.1 (R1.1), RN15.2 (R2.1), RN15.8 (R1.2)
unnamed: RN13.8 (R1.2), U10.15 (B3)
unnamed: RN13.2 (R2.1), RN15.3 (R3.1), RN15.7 (R2.2)
unnamed: RN13.7 (R2.2), U10.16 (B2)
unnamed: RN13.3 (R3.1), RN15.4 (R4.1), RN15.6 (R3.2)
unnamed: RN13.6 (R3.2), U10.17 (B1)
unnamed: R27.2, RN13.4 (R4.1), RN15.5 (R4.2)
unnamed: RN13.5 (R4.2), U10.18 (B0)
unnamed: RN14.1 (R1.1), RN16.2 (R2.1), RN16.8 (R1.2)
unnamed: RN14.8 (R1.2), U10.11 (B7)
unnamed: RN14.2 (R2.1), RN16.3 (R3.1), RN16.7 (R2.2)
unnamed: RN14.7 (R2.2), U10.12 (B6)
unnamed: RN14.3 (R3.1), RN16.4 (R4.1), RN16.6 (R3.2)
unnamed: RN14.6 (R3.2), U10.13 (B5)
unnamed: RN14.4 (R4.1), RN15.1 (R1.1), RN16.5 (R4.2)
unnamed: RN14.5 (R4.2), U10.14 (B4)

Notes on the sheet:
R2R DAC
